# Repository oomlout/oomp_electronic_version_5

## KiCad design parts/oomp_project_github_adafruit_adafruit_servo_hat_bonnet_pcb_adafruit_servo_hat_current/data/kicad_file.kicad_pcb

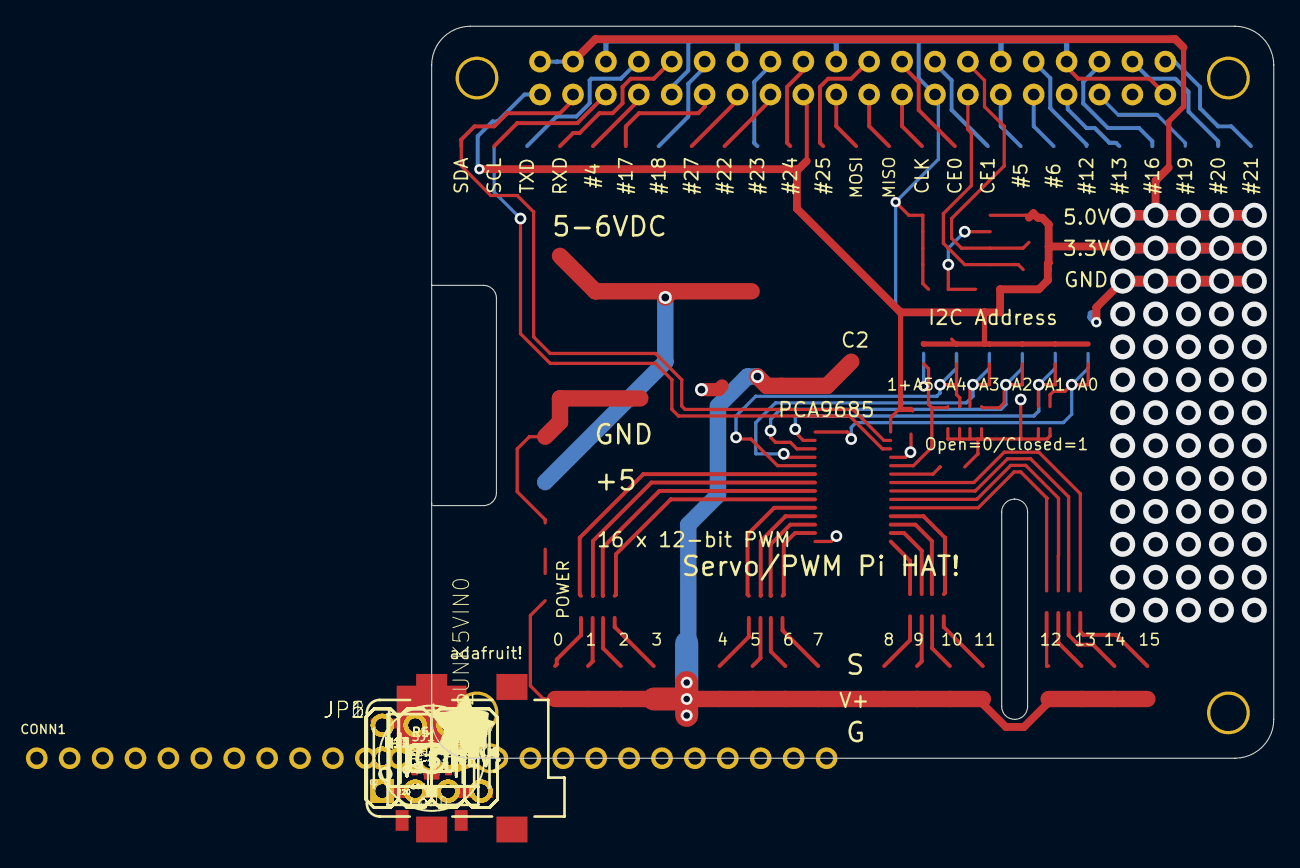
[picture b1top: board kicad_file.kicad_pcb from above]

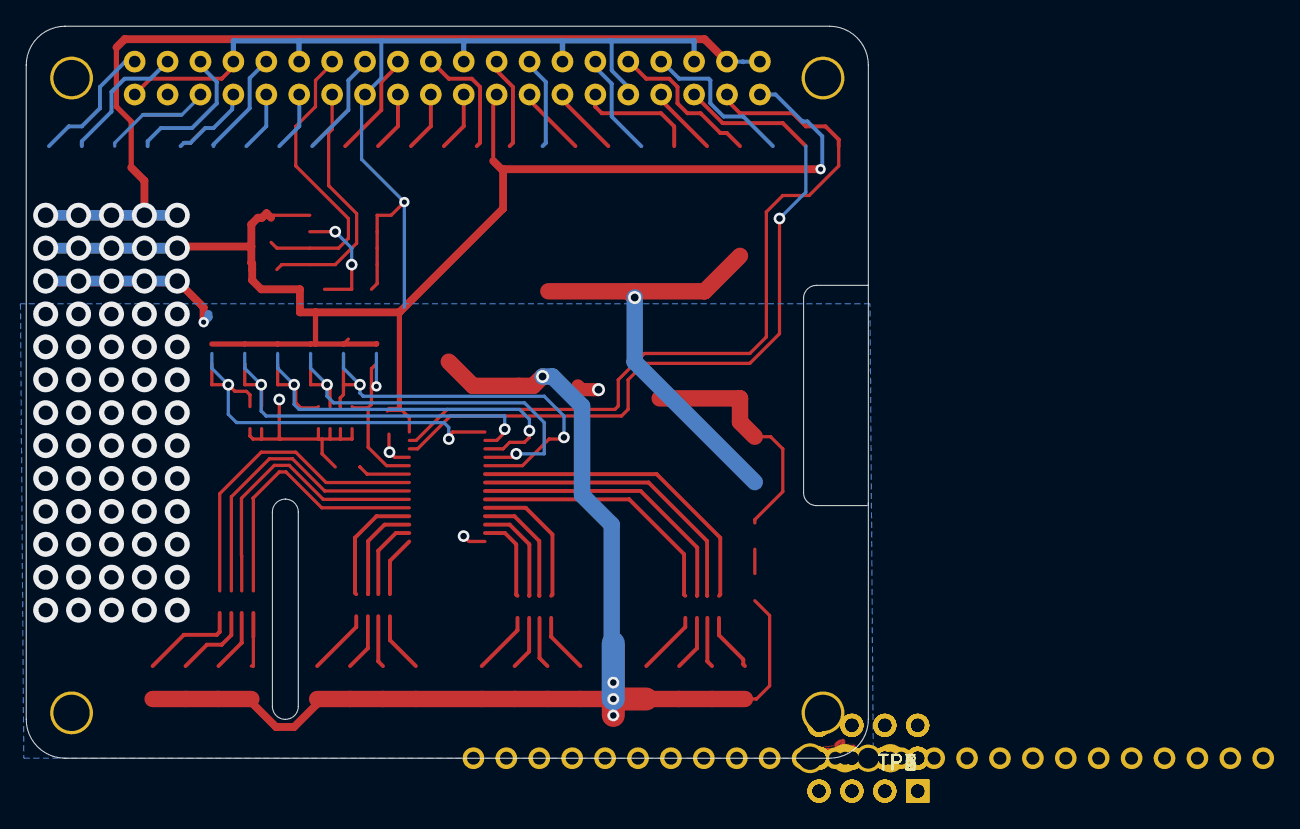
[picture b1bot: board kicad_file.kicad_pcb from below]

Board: 2 copper layers, 65.0 x 56.5 mm, 44 parts (6 on the bottom side), 73 nets.

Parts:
C1: 10uF; 0805-NO
C2: E3,5-8
CONN1: HEADER-1X25; 1X25_ROUND_70MIL
FID1, FID2, FID3: FIDUCIAL""; FIDUCIAL_1MM
JP1, JP2, JP5, JP6: 3X04
LED1: GREEN; CHIPLED_0805_NOOUTLINE
Q1: AOD417; TO252
R1, R2, R3: 3.9K; 0805-NO
R4, R5: 10K; RESPACK_4X0603
R7: 10K; 0805-NO
R10: 470; _0805MP
R11, R12, R13, R14: 220; RESPACK_4X0603
RPI1: RASPBERRYPI_BPLUS_HATSLOTS; PI_HAT_SLOTS
SJ1: WP; SOLDERJUMPER_CLOSEDWIRE
SJ_A0, SJ_A1, SJ_A2, SJ_A3, SJ_A4, SJ_A5: SOLDERJUMPER_REFLOW_NOPASTE
TP1, TP2, TP3, TP4, TP5, TP6: TPB1,27; B1,27
U1: CAT24C32; SOIC8_150MIL
U2: PCA9685; TSSOP28
U$5: PIHATLOGO
U$6: PCBFEAT-REV-056
U$51: ADAFRUIT_5MM
UNK5VIN0: 3.5mm term; TERMBLOCK_1X2-3.5MM
X1: 2.1mm SMT; DCJACK_2MM_SMT

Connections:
3.3V: C1.1, R1.2, R2.2, R3.2, RPI1.1, RPI1.17, SJ_A0.1, SJ_A1.1, SJ_A2.1, SJ_A3.1, SJ_A4.1, SJ_A5.1, U1.8, U2.28
5.0V: RPI1.2, RPI1.4
+5V: C2.+, JP1.2, JP1.5, JP1.8, JP1.11, JP2.2, JP2.5, JP2.8, JP2.11, JP5.2, JP5.5, JP5.8, JP5.11, JP6.2, JP6.5, JP6.8, JP6.11, LED1.A, Q1.2
A0: R5.7, SJ_A0.2, TP1.TP, U2.1
A1: R5.8, SJ_A1.2, TP2.TP, U2.2
A2: R4.5, SJ_A2.2, TP3.TP, U2.3
A3: R4.6, SJ_A3.2, TP4.TP, U2.4
A4: R4.7, SJ_A4.2, TP5.TP, U2.5
A5: R4.8, SJ_A5.2, TP6.TP, U2.24
EECLK: R2.1, RPI1.28, U1.6
EEDATA: R1.1, RPI1.27, U1.5
GND: C1.2, C2.-, JP1.3, JP1.6, JP1.9, JP1.12, JP2.3, JP2.6, JP2.9, JP2.12, JP5.3, JP5.6, JP5.9, JP5.12, JP6.3, JP6.6, JP6.9, JP6.12, Q1.1, R4.1, R4.2, R4.3, R4.4, R5.1, R5.2, R7.2, R10.2, RPI1.6, RPI1.9, RPI1.14, RPI1.20, RPI1.25, RPI1.30, RPI1.34, RPI1.39, SJ1.1, U1.1, U1.2, U1.3, U1.4, U2.14, U2.25, UNK5VIN0.2, X1.GND, X1.GNDBREAK
GPIO4: CONN1.5, RPI1.7
GPIO5: CONN1.18, RPI1.29
GPIO6: CONN1.19, RPI1.31
GPIO12: CONN1.20, RPI1.32
GPIO13: CONN1.21, RPI1.33
GPIO16: CONN1.22, RPI1.36
GPIO17: CONN1.6, RPI1.11
GPIO18: CONN1.7, RPI1.12
GPIO19: CONN1.23, RPI1.35
GPIO20: CONN1.24, RPI1.38
GPIO21: CONN1.25, RPI1.40
GPIO22: CONN1.9, RPI1.15
GPIO23: CONN1.10, RPI1.16
GPIO24: CONN1.11, RPI1.18
GPIO25: CONN1.12, RPI1.22
GPIO27: CONN1.8, RPI1.13
unnamed: R3.1, SJ1.2, U1.7
unnamed: LED1.C, R10.1
unnamed: JP1.4, R11.7
unnamed: JP1.1, R11.8
unnamed: JP1.7, R11.6
unnamed: JP1.10, R11.5
unnamed: JP2.1, R13.8
unnamed: JP2.4, R13.7
unnamed: JP2.7, R13.6
unnamed: JP2.10, R13.5
unnamed: JP6.10, R14.5
unnamed: JP6.7, R14.6
unnamed: JP6.4, R14.7
unnamed: JP6.1, R14.8
unnamed: JP5.10, R12.5
unnamed: JP5.7, R12.6
unnamed: JP5.4, R12.7
unnamed: JP5.1, R12.8
OE: R7.1, U2.23
PWM0: R13.4, U2.6
PWM1: R13.3, U2.7
PWM2: R13.2, U2.8
PWM3: R13.1, U2.9
PWM4: R11.4, U2.10
PWM5: R11.3, U2.11
PWM6: R11.2, U2.12
PWM7: R11.1, U2.13
PWM8: R14.4, U2.15
PWM9: R14.3, U2.16
PWM10: R14.2, U2.17
PWM11: R14.1, U2.18
PWM12: R12.4, U2.19
PWM13: R12.3, U2.20
PWM14: R12.2, U2.21
PWM15: R12.1, U2.22
PWRIN: Q1.3, UNK5VIN0.1, X1.PWR
RXD: CONN1.4, RPI1.10
SCL: CONN1.2, RPI1.5, U2.26
SDA: CONN1.1, RPI1.3, U2.27
SPI_CE0: CONN1.16, RPI1.24
SPI_CE1: CONN1.17, RPI1.26
SPI_MISO: CONN1.14, RPI1.21
SPI_MOSI: CONN1.13, RPI1.19
SPI_SCLK: CONN1.15, RPI1.23
TXD: CONN1.3, RPI1.8

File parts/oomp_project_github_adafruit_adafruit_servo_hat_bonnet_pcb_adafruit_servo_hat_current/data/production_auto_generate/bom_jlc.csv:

Comment,Designator,Footprint,LCSC Part #
,"JP1,JP2,JP5,JP6",Adafruit Servo HAT rev A-import-fps:3X04,
,U$51,Adafruit Servo HAT rev A-import-fps:ADAFRUIT_5MM,
,C2,"Adafruit Servo HAT rev A-import-fps:E3,5-8",
,U$6,Adafruit Servo HAT rev A-import-fps:PCBFEAT-REV-056,
,U$5,Adafruit Servo HAT rev A-import-fps:PIHATLOGO,
10K,R7,Adafruit Servo HAT rev A-import-fps:0805-NO,C17414
10K,"R4,R5",Adafruit Servo HAT rev A-import-fps:RESPACK_4X0603,C98220
10uF,C1,Adafruit Servo HAT rev A-import-fps:0805-NO,
2.1mm SMT,X1,Adafruit Servo HAT rev A-import-fps:DCJACK_2MM_SMT,
220,"R11,R12,R13,R14",Adafruit Servo HAT rev A-import-fps:RESPACK_4X0603,C2907127
3.5mm term,UNK5VIN0,Adafruit Servo HAT rev A-import-fps:TERMBLOCK_1X2-3.5MM,
3.9K,"R1,R2,R3",Adafruit Servo HAT rev A-import-fps:0805-NO,C2907252
470,R10,Adafruit Servo HAT rev A-import-fps:_0805MP,C17710
AOD417,Q1,Adafruit Servo HAT rev A-import-fps:TO252,
CAT24C32,U1,Adafruit Servo HAT rev A-import-fps:SOIC8_150MIL,
GREEN,LED1,Adafruit Servo HAT rev A-import-fps:CHIPLED_0805_NOOUTLINE,
HEADER-1X25,CONN1,Adafruit Servo HAT rev A-import-fps:1X25_ROUND_70MIL,C2883713
PCA9685,U2,Adafruit Servo HAT rev A-import-fps:TSSOP28,
RASPBERRYPI_BPLUS_HATSLOTS,RPI1,Adafruit Servo HAT rev A-import-fps:PI_HAT_SLOTS,
"TPB1,27","TP1,TP2,TP3,TP4,TP5,TP6","Adafruit Servo HAT rev A-import-fps:B1,27",

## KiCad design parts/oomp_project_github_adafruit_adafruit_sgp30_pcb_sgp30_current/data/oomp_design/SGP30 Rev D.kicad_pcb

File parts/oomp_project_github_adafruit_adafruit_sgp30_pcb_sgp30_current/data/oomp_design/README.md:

# OOMP KiCad design copy

Open `SGP30 Rev D.kicad_pro` (or the `.kicad_pcb` / `.kicad_sch`) in KiCad. Local OOMP libraries are under `libraries/`. Original inputs are preserved in [../original/](../original/).

Only verified unchanged installed KiCad defaults were renamed. Modified, custom, unmatched and unavailable items remain unchanged. Soldering variants are never swapped during conversion. Existing pad coordinates, nets and UUIDs are preserved.

See [conversion_report.yaml](conversion_report.yaml) for every conversion and skip. Copy this directory before editing; regeneration refuses to overwrite edited design files.

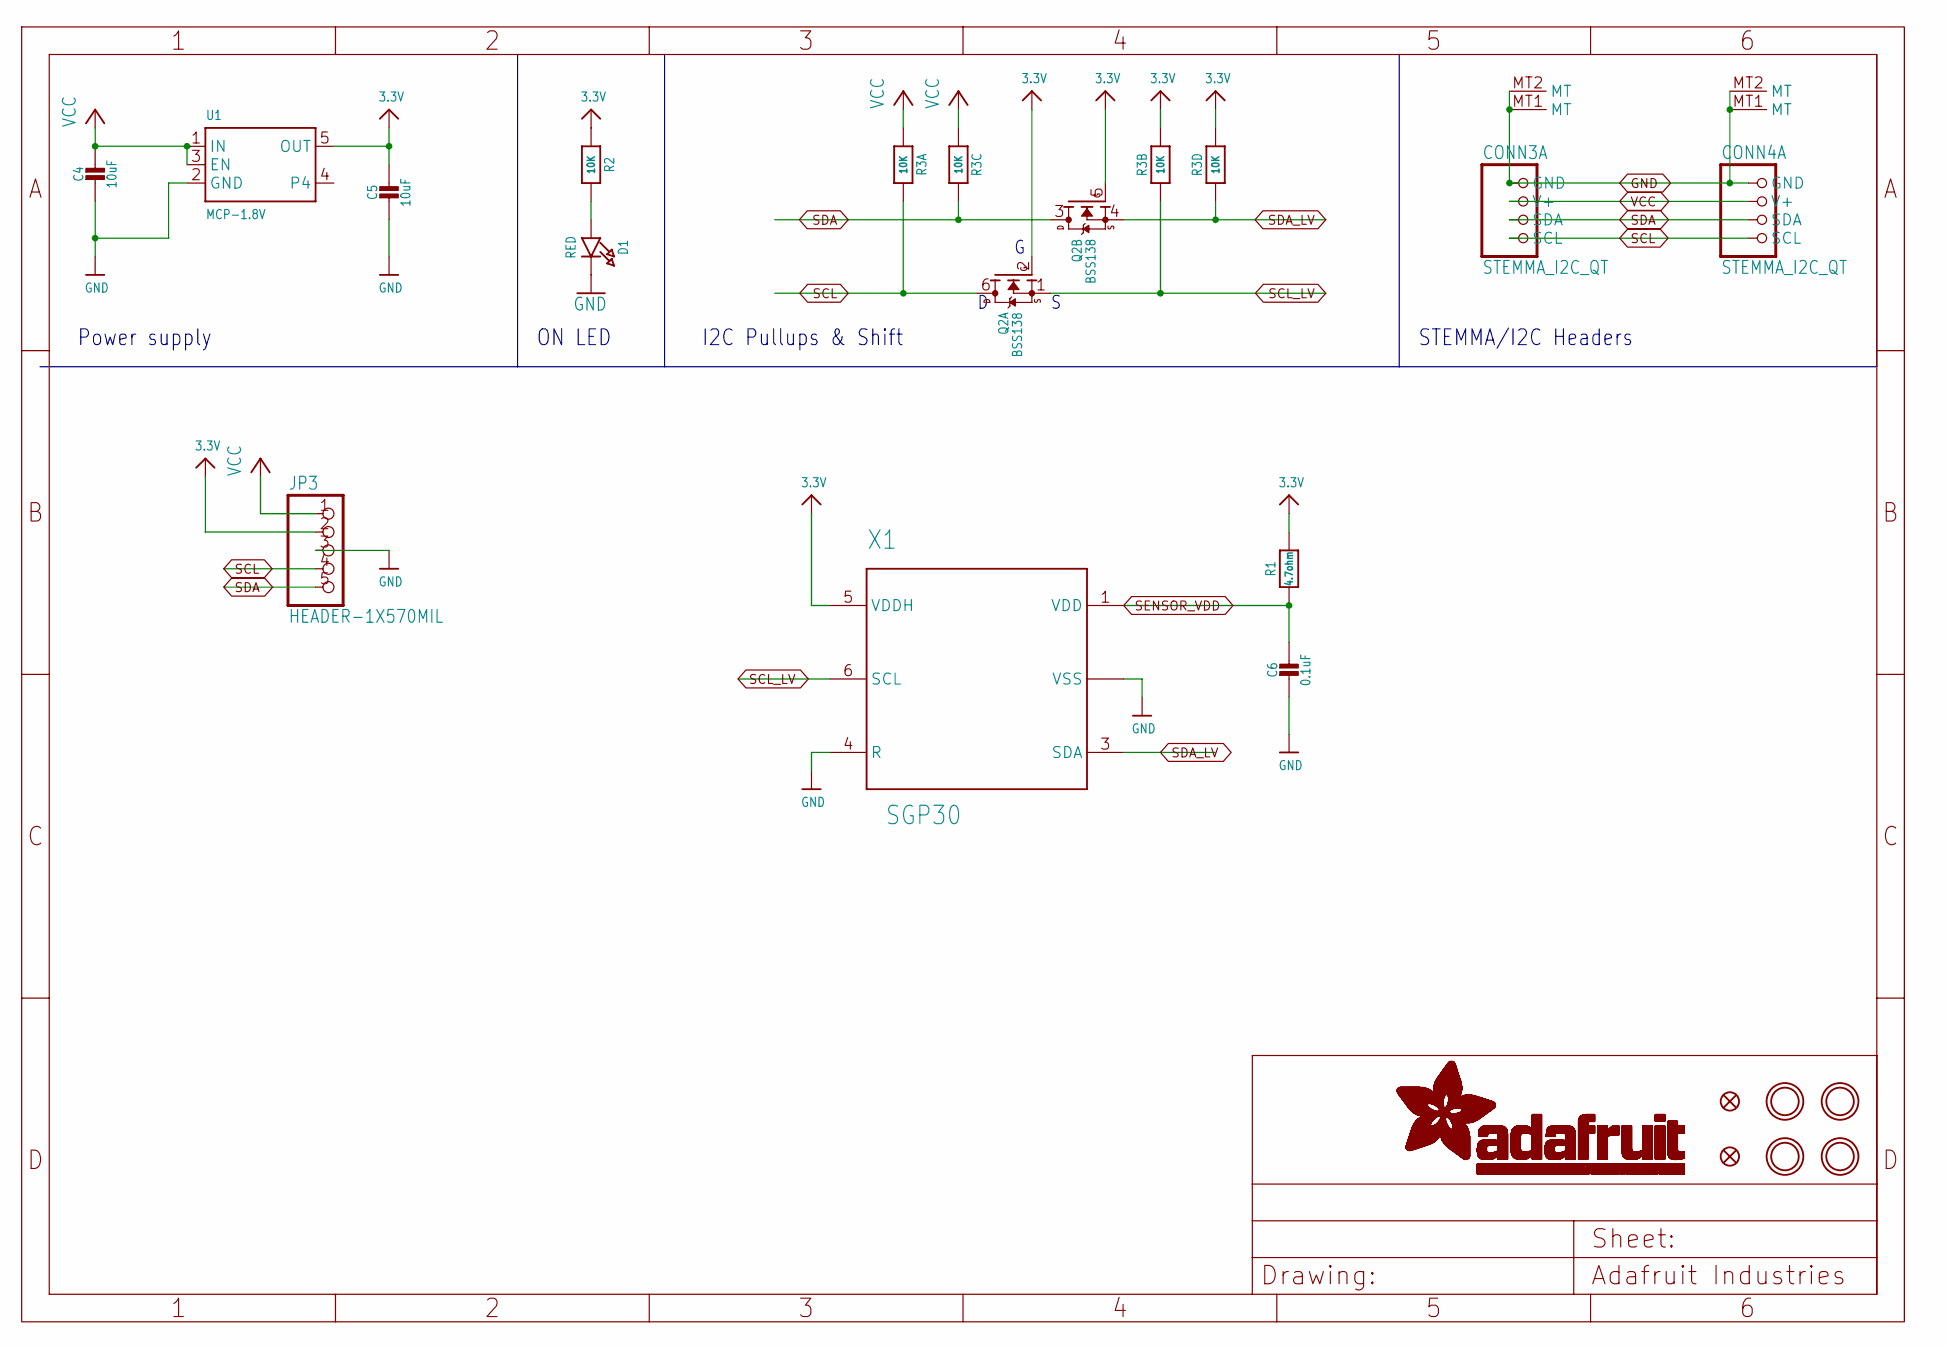
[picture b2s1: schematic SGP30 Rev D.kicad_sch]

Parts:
C4, C5: 10uF; 0805-NO
C6: 0.1uF; 0603-NO
CONN3, CONN4: STEMMA_I2C_QT; JST_SH4
D1: RED; CHIPLED_0603_NOOUTLINE
FID3, FID4: FIDUCIAL_1MM
JP3: HEADER-1X570MIL; 1X05_ROUND_70
Q2: BSS138; SOT363
R1: 4.7ohm; 0603-NO
R2: 10K; 0603-NO
R3: 10K; RESPACK_4X0603
U1: MCP-1.8V; SOT23-5
U$28, U$29, U$31, U$32: MOUNTINGHOLE2.5; MOUNTINGHOLE_2.5_PLATED
X1: SGP30

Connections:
3.3V: C5.1, JP3.2, Q2.2 (G), Q2.5 (G), R1.2, R2.1, R3.2 (1), R3.4 (1), U1.5 (OUT), X1.5 (VDDH)
GND: C4.2, C5.2, C6.2, CONN3.1 (GND), CONN3.MT1 (MT), CONN3.MT2 (MT), CONN4.1 (GND), CONN4.MT1 (MT), CONN4.MT2 (MT), D1.C, JP3.3, U1.2 (GND), X1.2 (VSS), X1.4 (R), X1.P$7 (VSS)
unnamed: D1.A, R2.2
SCL: CONN3.4 (SCL), CONN4.4 (SCL), JP3.4, Q2.6 (D), R3.8 (2)
SCL_LV: Q2.1 (S), R3.7 (2), X1.6 (SCL)
SDA: CONN3.3 (SDA), CONN4.3 (SDA), JP3.5, Q2.3 (D), R3.6 (2)
SDA_LV: Q2.4 (S), R3.5 (2), X1.3 (SDA)
SENSOR_VDD: C6.1, R1.1, X1.1 (VDD)
VCC: C4.1, CONN3.2 (V+), CONN4.2 (V+), JP3.1, R3.1, R3.3 (1), U1.1 (IN), U1.3 (EN)

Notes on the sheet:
I2C Pullups & Shift
Power supply
ON LED
STEMMA/I2C Headers

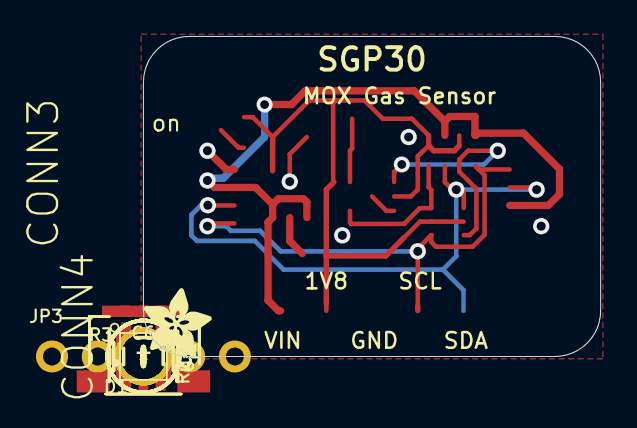
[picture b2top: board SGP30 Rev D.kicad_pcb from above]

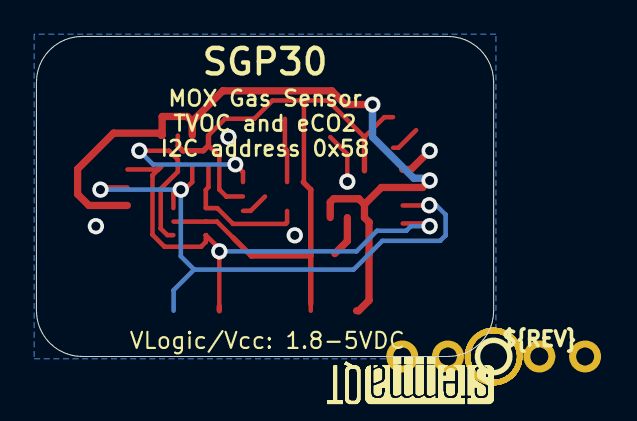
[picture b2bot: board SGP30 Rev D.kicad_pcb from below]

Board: 2 copper layers, 25.4 x 17.8 mm, 23 parts (3 on the bottom side), 9 nets.

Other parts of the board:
U$34: ADAFRUIT_3.5MM
U$35: PCBFEAT-REV-040
U$36, U$37: STEMMAQT

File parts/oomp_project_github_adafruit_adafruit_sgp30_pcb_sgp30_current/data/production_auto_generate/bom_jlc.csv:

Comment,Designator,Footprint,LCSC Part #
,JP3,SGP30 Rev D-import-fps:1X05_ROUND_70,C42431835
,U$34,SGP30 Rev D-import-fps:ADAFRUIT_3.5MM,
,U$35,SGP30 Rev D-import-fps:PCBFEAT-REV-040,
,"U$36,U$37",SGP30 Rev D-import-fps:STEMMAQT,
0.1uF,C6,SGP30 Rev D-import-fps:0603-NO,C14663
10K,R2,SGP30 Rev D-import-fps:0603-NO,C98220
10K,R3,SGP30 Rev D-import-fps:RESPACK_4X0603,C98220
10uF,"C4,C5",SGP30 Rev D-import-fps:0805-NO,
4.7ohm,R1,SGP30 Rev D-import-fps:0603-NO,
BSS138,Q2,SGP30 Rev D-import-fps:SOT363,
MCP-1.8V,U1,SGP30 Rev D-import-fps:SOT23-5,
RED,D1,SGP30 Rev D-import-fps:CHIPLED_0603_NOOUTLINE,
SGP30,X1,SGP30 Rev D-import-fps:SGP30,
STEMMA_I2C_QT,"CONN3,CONN4",SGP30 Rev D-import-fps:JST_SH4,C160404

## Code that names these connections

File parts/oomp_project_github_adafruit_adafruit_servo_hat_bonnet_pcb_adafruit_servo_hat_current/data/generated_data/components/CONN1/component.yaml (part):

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      position:
        x: 172.72
        y: 83.82
      net: GPIO4
      net_aliases:
      - GPIO4
      net_scope: global
      no_connect: false
      connected_to:
      - reference: RPI1
        pin_number: '7'
        pin_name: GPIO4
    - number: '6'
      name: '6'
      electrical_type: passive
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      position:
        x: 172.72
        y: 86.36
      net: GPIO17
      net_aliases:
      - GPIO17
      net_scope: global
      no_connect: false
      connected_to:
      - reference: RPI1
        pin_number: '11'
        pin_name: GPIO17
    - number: '7'
      name: '7'
      electrical_type: passive
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      position:
        x: 172.72
        y: 88.9
      net: GPIO18
      net_aliases:
      - GPIO18
      net_scope: global
      no_connect: false
      connected_to:
      - reference: RPI1
        pin_number: '12'
        pin_name: GPIO18
    - number: '8'
      name: '8'
      electrical_type: passive
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      position:
        x: 172.72
        y: 91.44
      net: GPIO27
      net_aliases:
      - GPIO27
      net_scope: global
      no_connect: false
      connected_to:
      - reference: RPI1
        pin_number: '13'
        pin_name: GPIO27
    - number: '9'
      name: '9'
      electrical_type: passive
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      position:
        x: 172.72
        y: 93.98
      net: GPIO22
      net_aliases:
      - GPIO22
      net_scope: global
      no_connect: false
      connected_to:
      - reference: RPI1
        pin_number: '15'
        pin_name: GPIO22
    - number: '10'
      name: '10'
      electrical_type: passive
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      position:
        x: 172.72
        y: 96.52
      net: GPIO23
      net_aliases:
      - GPIO23
      net_scope: global
      no_connect: false
      connected_to:
      - reference: RPI1
        pin_number: '16'
        pin_name: GPIO23
    - number: '11'
      name: '11'
      electrical_type: passive
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      position:
        x: 172.72
        y: 99.06
      net: GPIO24
      net_aliases:
      - GPIO24
      net_scope: global
      no_connect: false
      connected_to:
      - reference: RPI1
        pin_number: '18'
        pin_name: GPIO24
    - number: '12'
      name: '12'
      electrical_type: passive
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      position:
        x: 172.72
        y: 101.6
      net: GPIO25
      net_aliases:
      - GPIO25
      net_scope: global
      no_connect: false
      connected_to:
      - reference: RPI1
        pin_number: '22'
        pin_name: GPIO25
    - number: '13'
      name: '13'
      electrical_type: passive
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      connected_to:
      - reference: RPI1
        pin_number: '19'
        pin_name: SPI_MOSI
    - number: '14'
      name: '14'
      electrical_type: passive
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      connected_to:
      - reference: RPI1
        pin_number: '21'
        pin_name: SPI_MISO
    - number: '15'
      name: '15'
      electrical_type: passive
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      connected_to:
      - reference: RPI1
        pin_number: '23'
        pin_name: SPI_SCLK
    - number: '16'
      name: '16'
      electrical_type: passive
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      connected_to:
      - reference: RPI1
        pin_number: '24'
        pin_name: '#SPI_CE0'
    - number: '17'
      name: '17'
      electrical_type: passive
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      connected_to:
      - reference: RPI1
        pin_number: '26'
        pin_name: '#SPI_CE1'
    - number: '18'
      name: '18'
      electrical_type: passive
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      position:
        x: 172.72
        y: 116.84
      net: GPIO5
      net_aliases:
      - GPIO5
      net_scope: global
      no_connect: false
      connected_to:
      - reference: RPI1
        pin_number: '29'
        pin_name: GPIO5
    - number: '19'
      name: '19'
      electrical_type: passive
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      position:
        x: 172.72
        y: 119.38
      net: GPIO6
      net_aliases:
      - GPIO6
      net_scope: global
      no_connect: false
      connected_to:
      - reference: RPI1
        pin_number: '31'
        pin_name: GPIO6
    - number: '20'
      name: '20'
      electrical_type: passive
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      position:
        x: 172.72
        y: 121.92
      net: GPIO12
      net_aliases:
      - GPIO12
      net_scope: global
      no_connect: false
      connected_to:
      - reference: RPI1
        pin_number: '32'
        pin_name: GPIO12
    - number: '21'
      name: '21'
      electrical_type: passive
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      position:
        x: 172.72
        y: 124.46
      net: GPIO13
      net_aliases:
      - GPIO13
      net_scope: global
      no_connect: false
      connected_to:
      - reference: RPI1
        pin_number: '33'
        pin_name: GPIO13
    - number: '22'
      name: '22'
      electrical_type: passive
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      position:
        x: 172.72
        y: 127.0
      net: GPIO16
      net_aliases:
      - GPIO16
      net_scope: global
      no_connect: false
      connected_to:
      - reference: RPI1
        pin_number: '36'
        pin_name: GPIO16
    - number: '23'
      name: '23'
      electrical_type: passive
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      position:
        x: 172.72
        y: 129.54
      net: GPIO19
      net_aliases:
      - GPIO19
      net_scope: global
      no_connect: false
      connected_to:
      - reference: RPI1
        pin_number: '35'
        pin_name: GPIO19
    - number: '24'
      name: '24'
      electrical_type: passive
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      position:
        x: 172.72
        y: 132.08
      net: GPIO20
      net_aliases:
      - GPIO20
      net_scope: global
      no_connect: false
      connected_to:
      - reference: RPI1
        pin_number: '38'
        pin_name: GPIO20
    - number: '25'
      name: '25'
      electrical_type: passive
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      position:
        x: 172.72
        y: 134.62
      net: GPIO21
      net_aliases:
      - GPIO21
      net_scope: global
      no_connect: false
      connected_to:
      - reference: RPI1
        pin_number: '40'
        pin_name: GPIO21
    size:
      local_graphics:
        measurement: symbol graphics only; excludes pins, properties, and text
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    pin_name: RXD
  - reference: RPI1
    pin_number: '11'
    pin_name: GPIO17
  - reference: RPI1
    pin_number: '12'
    pin_name: GPIO18
  - reference: RPI1
    pin_number: '13'
    pin_name: GPIO27
  - reference: RPI1
    pin_number: '15'
    pin_name: GPIO22
  - reference: RPI1
    pin_number: '16'
    pin_name: GPIO23
  - reference: RPI1
    pin_number: '18'
    pin_name: GPIO24
  - reference: RPI1
    pin_number: '19'
    pin_name: SPI_MOSI
  - reference: RPI1
    pin_number: '21'
    pin_name: SPI_MISO
  - reference: RPI1
    pin_number: '22'
    pin_name: GPIO25
  - reference: RPI1
    pin_number: '23'
    pin_name: SPI_SCLK
  - reference: RPI1
    pin_number: '24'
    pin_name: '#SPI_CE0'
  - reference: RPI1
    pin_number: '26'
    pin_name: '#SPI_CE1'
  - reference: RPI1
    pin_number: '29'
    pin_name: GPIO5
  - reference: RPI1
    pin_number: '3'
    pin_name: SDA
  - reference: RPI1
    pin_number: '31'
    pin_name: GPIO6
  - reference: RPI1
    pin_number: '32'
    pin_name: GPIO12
  - reference: RPI1
    pin_number: '33'
    pin_name: GPIO13
  - reference: RPI1
    pin_number: '35'
    pin_name: GPIO19
  - reference: RPI1
    pin_number: '36'
    pin_name: GPIO16
  - reference: RPI1
    pin_number: '38'
    pin_name: GPIO20
  - reference: RPI1
    pin_number: '40'
    pin_name: GPIO21
  - reference: RPI1
    pin_number: '5'
    pin_name: SCL
  - reference: RPI1
    pin_number: '7'
    pin_name: GPIO4
  - reference: RPI1
    pin_number: '8'
    pin_name: TXD
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    layers:
    - '*.Cu'
    - '*.Mask'
    net: GPIO4
    net_number: null
    pin_function: null
    pin_type: null
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    layers:
    - '*.Cu'
    - '*.Mask'
    net: GPIO17
    net_number: null
    pin_function: null
    pin_type: null
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    layers:
    - '*.Cu'
    - '*.Mask'
    net: GPIO18
    net_number: null
    pin_function: null
    pin_type: null
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    layers:
    - '*.Cu'
    - '*.Mask'
    net: GPIO27
    net_number: null
    pin_function: null
    pin_type: null
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    layers:
    - '*.Cu'
    - '*.Mask'
    net: GPIO22
    net_number: null
    pin_function: null
    pin_type: null
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    layers:
    - '*.Cu'
    - '*.Mask'
    net: GPIO23
    net_number: null
    pin_function: null
    pin_type: null
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    layers:
    - '*.Cu'
    - '*.Mask'
    net: GPIO24
    net_number: null
    pin_function: null
    pin_type: null
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    layers:
    - '*.Cu'
    - '*.Mask'
    net: GPIO25
    net_number: null
    pin_function: null
    pin_type: null
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    layers:
    - '*.Cu'
    - '*.Mask'
    net: GPIO5
    net_number: null
    pin_function: null
    pin_type: null
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    layers:
    - '*.Cu'
    - '*.Mask'
    net: GPIO6
    net_number: null
    pin_function: null
    pin_type: null
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    layers:
    - '*.Cu'
    - '*.Mask'
    net: GPIO12
    net_number: null
    pin_function: null
    pin_type: null
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    layers:
    - '*.Cu'
    - '*.Mask'
    net: GPIO13
    net_number: null
    pin_function: null
    pin_type: null
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    layers:
    - '*.Cu'
    - '*.Mask'
    net: GPIO16
    net_number: null
    pin_function: null
    pin_type: null
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    layers:
    - '*.Cu'
    - '*.Mask'
    net: GPIO19
    net_number: null
    pin_function: null
    pin_type: null
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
